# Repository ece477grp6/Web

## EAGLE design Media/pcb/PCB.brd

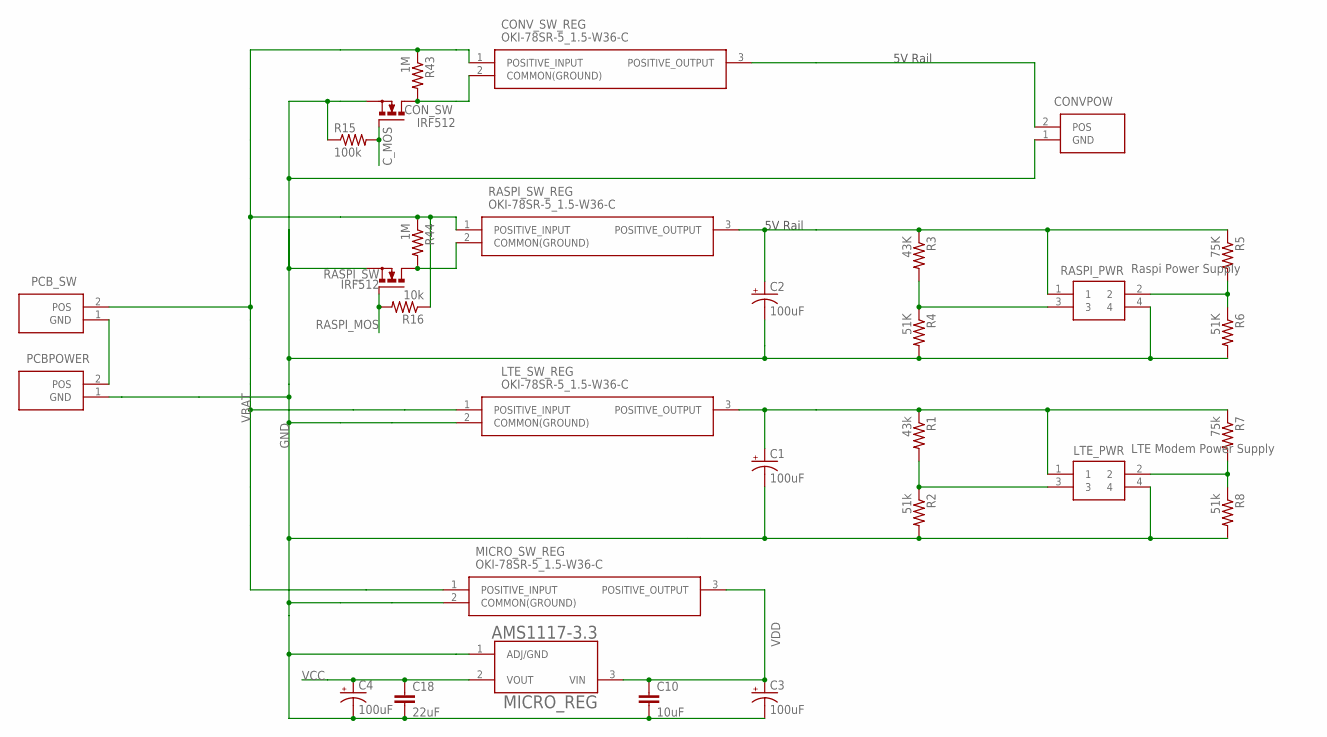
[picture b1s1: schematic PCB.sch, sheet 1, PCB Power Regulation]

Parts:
C1, C2, C3, C4: 100uF; 140CLH-0810
C10: 10uF; C0805
C18: 22uF; C0805
CONVPOW: PRT-10474; SHDR2W320P716_1X2_1574X813X158
CONV_SW_REG: OKI-78SR-5_1.5-W36-C; OKI-78SR
CON_SW: IRF512; TO220BV
LTE_PWR: LTE Modem Power Supply; 105057-0001
LTE_SW_REG: OKI-78SR-5_1.5-W36-C; OKI-78SR
MICRO_REG: AMS1117-3.3; SOT229P700X180-4N
MICRO_SW_REG: OKI-78SR-5_1.5-W36-C; OKI-78SR
PCBPOWER: PRT-10474; SHDR2W320P716_1X2_1574X813X158
PCB_SW: PRT-10474; SHDR2W320P716_1X2_1574X813X158
R1: 43k; R0805
R2, R8: 51k; R0805
R3: 43K; R0805
R4, R6: 51K; R0805
R5: 75K; R0805
R7: 75k; R0805
R15: 100k; R0805
R16: 10k; R0805
R43, R44: 1M; R0805
RASPI_PWR: Raspi Power Supply; 105057-0001
RASPI_SW: IRF512; TO220BV
RASPI_SW_REG: OKI-78SR-5_1.5-W36-C; OKI-78SR

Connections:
C_MOS: CON_SW.G, R15.2; also elsewhere on the board
GND: C1.-, C2.-, C3.-, C4.-, C10.2, C18.2, CONVPOW.1 (GND), CON_SW.S, LTE_PWR.4, LTE_SW_REG.2 (COMMON(GROUND)), MICRO_REG.1 (ADJ/GND), MICRO_SW_REG.2 (COMMON(GROUND)), PCBPOWER.1 (GND), R2.2, R4.2, R6.2, R8.2, R15.1, RASPI_PWR.4, RASPI_SW.S; also elsewhere on the board
unnamed: CONVPOW.2 (POS), CONV_SW_REG.3 (POSITIVE_OUTPUT)
unnamed: C1.+, LTE_PWR.1, LTE_SW_REG.3 (POSITIVE_OUTPUT), R1.1, R7.1
unnamed: LTE_PWR.3, R1.2, R2.1
unnamed: LTE_PWR.2, R7.2, R8.1
unnamed: CONV_SW_REG.2 (COMMON(GROUND)), CON_SW.D, R43.2
unnamed: R5.2, R6.1, RASPI_PWR.2
unnamed: R3.2, R4.1, RASPI_PWR.3
unnamed: C2.+, R3.1, R5.1, RASPI_PWR.1, RASPI_SW_REG.3 (POSITIVE_OUTPUT)
unnamed: R44.2, RASPI_SW.D, RASPI_SW_REG.2 (COMMON(GROUND))
unnamed: PCBPOWER.2 (POS), PCB_SW.1 (GND)
RASPI_MOS: R16.2, RASPI_SW.G; also elsewhere on the board
VBAT: CONV_SW_REG.1 (POSITIVE_INPUT), LTE_SW_REG.1 (POSITIVE_INPUT), MICRO_SW_REG.1 (POSITIVE_INPUT), PCB_SW.2 (POS), R16.1, R43.1, R44.1, RASPI_SW_REG.1 (POSITIVE_INPUT)
VCC: C4.+, C18.1, MICRO_REG.2 (VOUT); also elsewhere on the board
VDD: C3.+, C10.1, MICRO_REG.3 (VIN), MICRO_SW_REG.3 (POSITIVE_OUTPUT); also elsewhere on the board

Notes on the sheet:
5V Rail

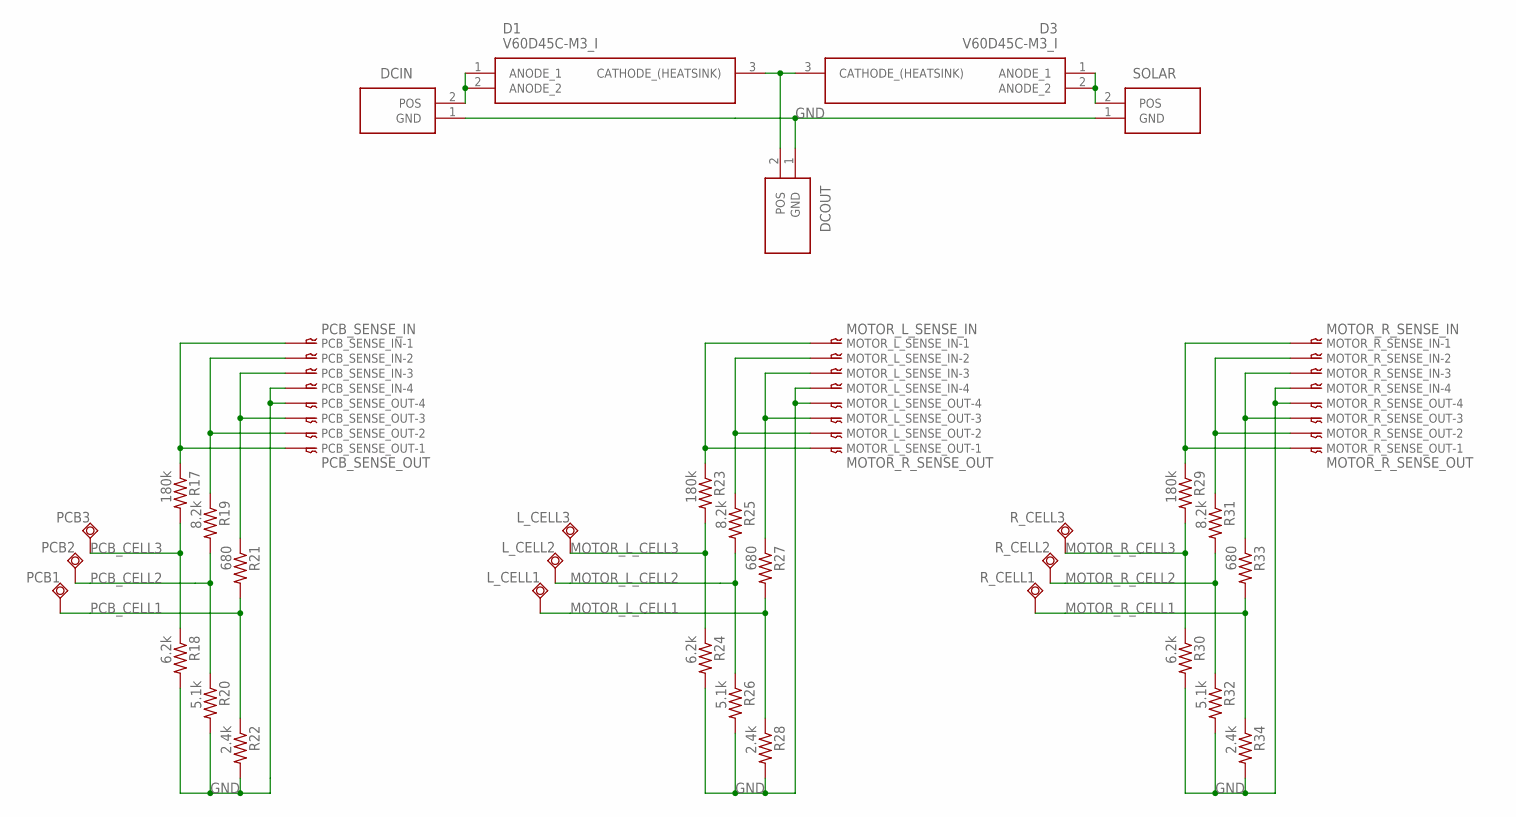
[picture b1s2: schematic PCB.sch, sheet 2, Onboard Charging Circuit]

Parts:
D1, D3: V60D45C-M3_I; TO-263AC(SMPD)
DCIN: PRT-10474; SHDR2W320P716_1X2_1574X813X158
DCOUT: PRT-10474; SHDR2W320P716_1X2_1574X813X158
L_CELL1, L_CELL2: TPSQB2,54; B2,54
L_CELL3: PCB_CELL3; B2,54
MOTOR_L_SENSE_IN: MOTOR_L_SENSE_IN; B4B-XH
MOTOR_L_SENSE_OUT: MOTOR_R_SENSE_OUT; B4B-XH
MOTOR_R_SENSE_IN: MOTOR_R_SENSE_IN; B4B-XH
MOTOR_R_SENSE_OUT: MOTOR_R_SENSE_OUT; B4B-XH
PCB1, PCB2: TPSQB2,54; B2,54
PCB3: PCB_CELL3; B2,54
PCB_SENSE_IN: PCB_SENSE_IN; B4B-XH
PCB_SENSE_OUT: PCB_SENSE_OUT; B4B-XH
R17, R23, R29: 180k; R0805
R18, R24, R30: 6.2k; R0805
R19, R25, R31: 8.2k; R0805
R20, R26, R32: 5.1k; R0805
R21, R27, R33: 680; R0805
R22, R28, R34: 2.4k; R0805
R_CELL1, R_CELL2: TPSQB2,54; B2,54
R_CELL3: PCB_CELL3; B2,54
SOLAR: PRT-10474; SHDR2W320P716_1X2_1574X813X158

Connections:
GND: DCIN.1 (GND), DCOUT.1 (GND), MOTOR_L_SENSE_IN.P$4, MOTOR_L_SENSE_OUT.P$4, MOTOR_R_SENSE_IN.P$4, MOTOR_R_SENSE_OUT.P$4, PCB_SENSE_IN.P$4, PCB_SENSE_OUT.P$4, R18.2, R20.2, R22.2, R24.2, R26.2, R28.2, R30.2, R32.2, R34.2, SOLAR.1 (GND); also elsewhere on the board
MOTOR_L_CELL1: L_CELL1.TP, R27.2, R28.1; also elsewhere on the board
MOTOR_L_CELL2: L_CELL2.TP, R25.2, R26.1; also elsewhere on the board
MOTOR_L_CELL3: L_CELL3.TP, R23.2, R24.1; also elsewhere on the board
MOTOR_R_CELL1: R33.2, R34.1, R_CELL1.TP; also elsewhere on the board
MOTOR_R_CELL2: R31.2, R32.1, R_CELL2.TP; also elsewhere on the board
MOTOR_R_CELL3: R29.2, R30.1, R_CELL3.TP; also elsewhere on the board
unnamed: PCB_SENSE_IN.P$3, PCB_SENSE_OUT.P$3, R21.1
unnamed: D1.1 (ANODE_1), D1.2 (ANODE_2), DCIN.2 (POS)
unnamed: D3.1 (ANODE_1), D3.2 (ANODE_2), SOLAR.2 (POS)
unnamed: PCB_SENSE_IN.P$1, PCB_SENSE_OUT.P$1, R17.1
unnamed: MOTOR_L_SENSE_IN.P$3, MOTOR_L_SENSE_OUT.P$3, R27.1
unnamed: MOTOR_L_SENSE_IN.P$2, MOTOR_L_SENSE_OUT.P$2, R25.1
unnamed: MOTOR_L_SENSE_IN.P$1, MOTOR_L_SENSE_OUT.P$1, R23.1
unnamed: MOTOR_R_SENSE_IN.P$3, MOTOR_R_SENSE_OUT.P$3, R33.1
unnamed: MOTOR_R_SENSE_IN.P$2, MOTOR_R_SENSE_OUT.P$2, R31.1
unnamed: PCB_SENSE_IN.P$2, PCB_SENSE_OUT.P$2, R19.1
unnamed: MOTOR_R_SENSE_IN.P$1, MOTOR_R_SENSE_OUT.P$1, R29.1
unnamed: D1.3 (CATHODE_(HEATSINK)), D3.3 (CATHODE_(HEATSINK)), DCOUT.2 (POS)
PCB_CELL1: PCB1.TP, R21.2, R22.1; also elsewhere on the board
PCB_CELL2: PCB2.TP, R19.2, R20.1; also elsewhere on the board
PCB_CELL3: PCB3.TP, R17.2, R18.1; also elsewhere on the board

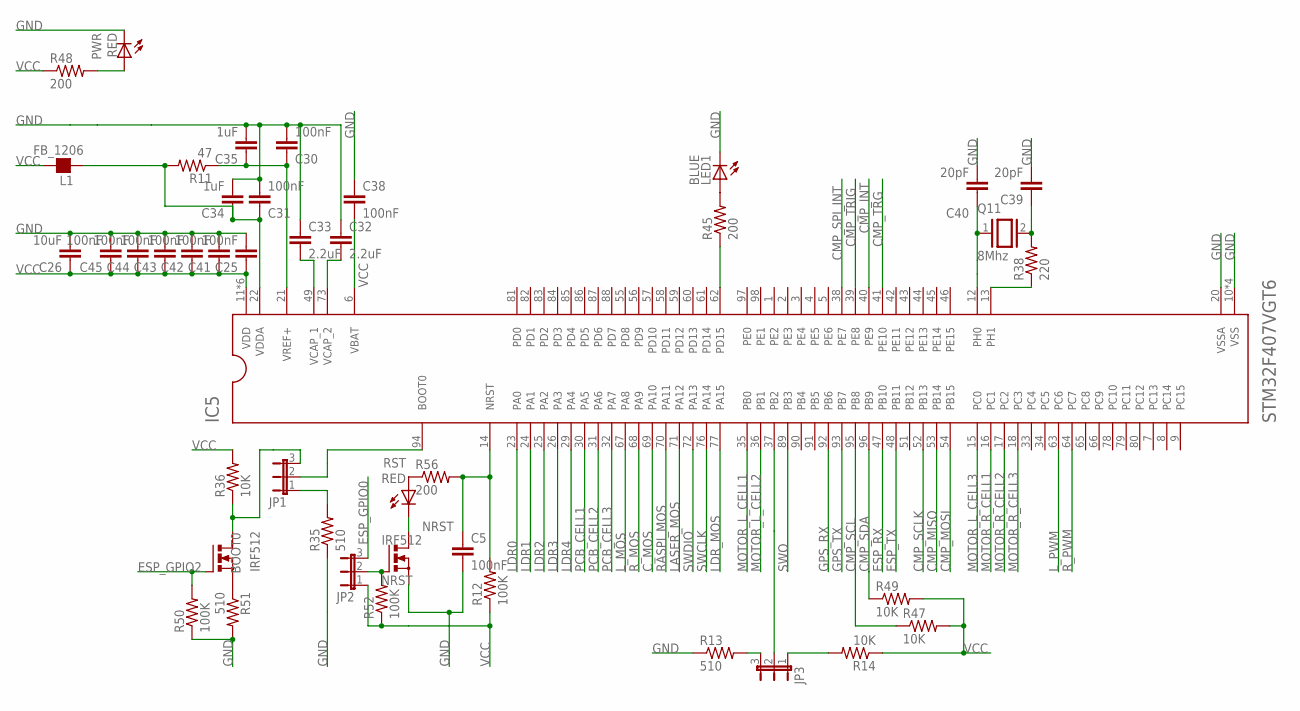
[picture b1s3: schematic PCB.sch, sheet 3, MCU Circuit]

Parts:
BOOT0: IRF512; TO220BV
C5, C25, C30, C31, C38, C41, C42, C43, C44, C45: 100nF; C0805
C26: 10uF; C0805
C32, C33: 2.2uF; C0805
C34, C35: 1uF; C0805
C39, C40: 20pF; C0805
IC5: STM32F407VGT6; QFP50P1600X1600X160-100N
JP1, JP2, JP3: JP2E; JP2
L1: FB_1206; L1206
LED1: BLUE; CHIPLED_0805
NRST: IRF512; TO220BV
PWR: RED; CHIPLED_0805
Q11: 8Mhz; QS
R11: 47; R0805
R12, R50, R52: 100K; R0805
R13, R35, R51: 510; R0805
R14, R36, R47, R49: 10K; R0805
R38: 220; R0805
R45, R48, R56: 200; R0805
RST: RED; CHIPLED_0805

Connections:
CMP_INT: IC5.40 (PE9); also elsewhere on the board
CMP_MISO: IC5.53 (PB14); also elsewhere on the board
CMP_MOSI: IC5.54 (PB15); also elsewhere on the board
CMP_SCL: IC5.95 (PB8), R47.1; also elsewhere on the board
CMP_SCLK: IC5.52 (PB13); also elsewhere on the board
CMP_SDA: IC5.96 (PB9), R49.1; also elsewhere on the board
CMP_SPI_INT: IC5.38 (PE7); also elsewhere on the board
CMP_TRG: IC5.41 (PE10); also elsewhere on the board
CMP_TRIG: IC5.39 (PE8); also elsewhere on the board
C_MOS: IC5.69 (PA10); also elsewhere on the board
ESP_GPIO0: JP2.3; also elsewhere on the board
ESP_GPIO2: BOOT0.G, R50.2; also elsewhere on the board
ESP_RX: IC5.47 (PB10); also elsewhere on the board
ESP_TX: IC5.48 (PB11); also elsewhere on the board
GND: C5.2, C25.2, C26.2, C30.2, C31.2, C32.1, C33.1, C34.2, C35.2, C38.1, C39.2, C40.2, C41.2, C42.2, C43.2, C44.2, C45.2, IC5.10 (VSS), IC5.20 (VSSA), IC5.27 (VSS), IC5.74 (VSS), IC5.99 (VSS), LED1.C, NRST.S, PWR.C, R13.1, R35.1, R50.1, R51.2; also elsewhere on the board
GPS_RX: IC5.92 (PB6); also elsewhere on the board
GPS_TX: IC5.93 (PB7); also elsewhere on the board
LASER_MOS: IC5.71 (PA12); also elsewhere on the board
LDR0: IC5.23 (PA0); also elsewhere on the board
LDR1: IC5.24 (PA1); also elsewhere on the board
LDR2: IC5.25 (PA2); also elsewhere on the board
LDR3: IC5.26 (PA3); also elsewhere on the board
LDR4: IC5.29 (PA4); also elsewhere on the board
LDR_MOS: IC5.77 (PA15); also elsewhere on the board
L_MOS: IC5.67 (PA8); also elsewhere on the board
L_PWM: IC5.63 (PC6); also elsewhere on the board
MOTOR_L_CELL1: IC5.35 (PB0); also elsewhere on the board
MOTOR_L_CELL2: IC5.36 (PB1); also elsewhere on the board
MOTOR_L_CELL3: IC5.15 (PC0); also elsewhere on the board
MOTOR_R_CELL1: IC5.16 (PC1); also elsewhere on the board
MOTOR_R_CELL2: IC5.17 (PC2); also elsewhere on the board
MOTOR_R_CELL3: IC5.18 (PC3); also elsewhere on the board
unnamed: IC5.37 (PB2), JP3.2
unnamed: C32.2, IC5.73 (VCAP_2)
unnamed: R56.1, RST.A
unnamed: C33.2, IC5.49 (VCAP_1)
unnamed: PWR.A, R48.2
unnamed: JP3.1, R14.2
unnamed: C30.1, C35.1, IC5.21 (VREF+), R11.1
unnamed: C31.1, C34.1, IC5.22 (VDDA), L1.1, R11.2
unnamed: IC5.62 (PD15), R45.1
unnamed: JP2.2, NRST.G, R52.2
unnamed: BOOT0.S, R51.1
unnamed: LED1.A, R45.2
unnamed: C5.1, IC5.14 (NRST), R12.2, R56.2
unnamed: IC5.13 (PH1), R38.1
unnamed: IC5.94 (BOOT0), JP1.2
unnamed: JP1.1, R35.2
unnamed: C39.1, Q11.2, R38.2
unnamed: BOOT0.D, JP1.3, R36.1
unnamed: C40.1, IC5.12 (PH0), Q11.1
unnamed: JP3.3, R13.2
NRST: NRST.D, RST.C; also elsewhere on the board
PCB_CELL1: IC5.30 (PA5); also elsewhere on the board
PCB_CELL2: IC5.31 (PA6); also elsewhere on the board
PCB_CELL3: IC5.32 (PA7); also elsewhere on the board
RASPI_MOS: IC5.70 (PA11); also elsewhere on the board
R_MOS: IC5.68 (PA9); also elsewhere on the board
R_PWM: IC5.64 (PC7); also elsewhere on the board
SWCLK: IC5.76 (PA14); also elsewhere on the board
SWDIO: IC5.72 (PA13); also elsewhere on the board
SWO: IC5.89 (PB3); also elsewhere on the board
VCC: C25.1, C26.1, C38.2, C41.1, C42.1, C43.1, C44.1, C45.1, IC5.6 (VBAT), IC5.11 (VDD), IC5.19 (VDD), IC5.28 (VDD), IC5.50 (VDD), IC5.75 (VDD), IC5.100 (VDD), JP2.1, L1.2, R12.1, R14.1, R36.2, R47.2, R48.1, R49.2, R52.1; also elsewhere on the board

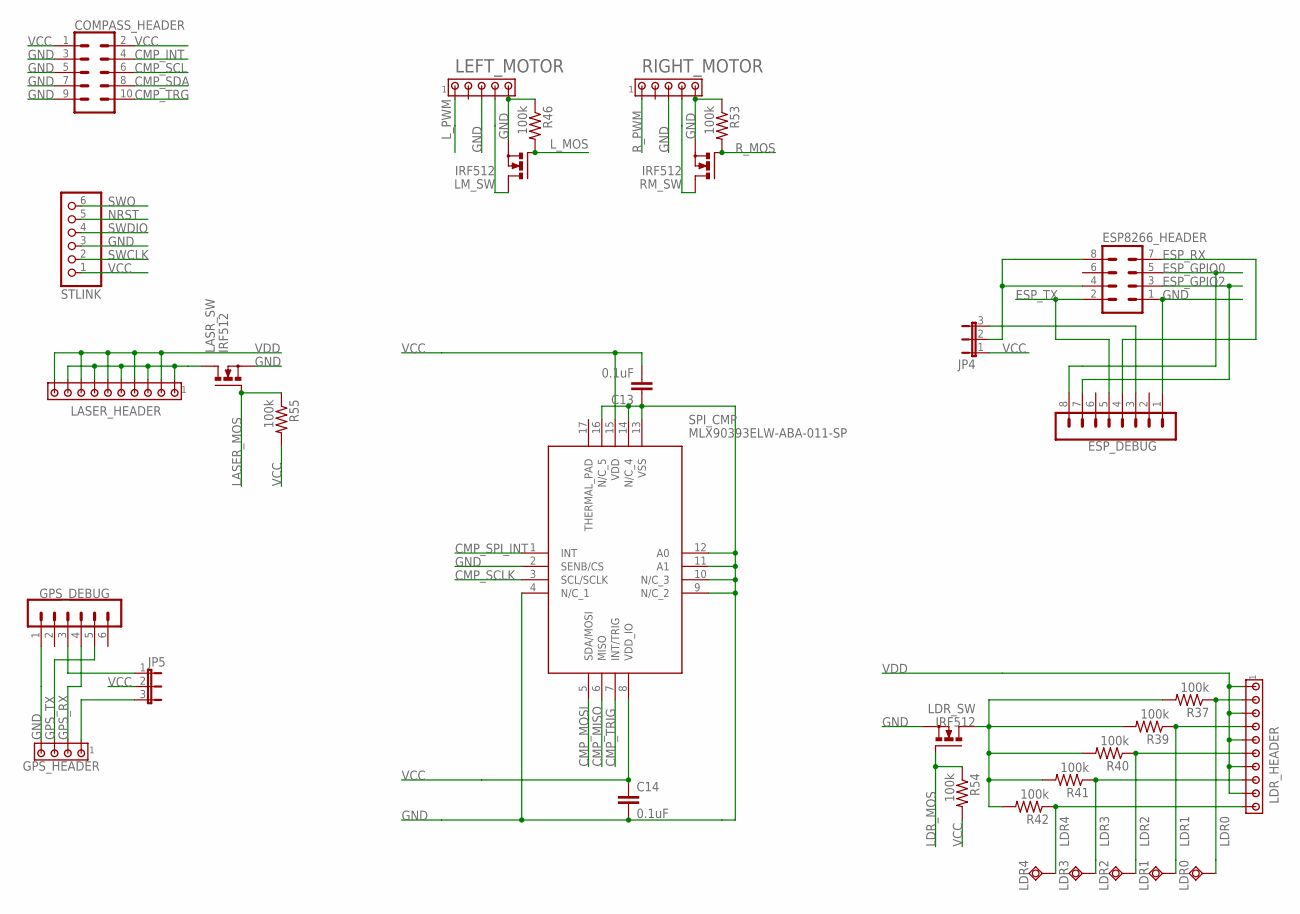
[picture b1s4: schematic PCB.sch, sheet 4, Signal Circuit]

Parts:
C13, C14: 0.1uF; C1206
COMPASS_HEADER: CONN_05X2SHD; 2X5-SHROUDED
ESP8266_HEADER: MA04-2
ESP_DEBUG: MA08-1
GPS_DEBUG: MA06-1
GPS_HEADER: MTA04-100; 10X04MTA
JP4, JP5: JP2E; JP2
LASER_HEADER: MTA10-100; 10X10MTA
LASR_SW: IRF512; TO220BV
LDR0, LDR1, LDR2, LDR3, LDR4: TPSQB2,54; B2,54
LDR_HEADER: MTA10-100; 10X10MTA
LDR_SW: IRF512; TO220BV
LEFT_MOTOR: MTA05-100; 1X05MTA
LM_SW: IRF512; TO220BV
R37, R39, R40, R41, R42, R46, R53, R54, R55: 100k; R1206
RIGHT_MOTOR: MTA05-100; 1X05MTA
RM_SW: IRF512; TO220BV
SPI_CMP: MLX90393ELW-ABA-011-SP; QFN50P300X300X100-17N
STLINK: PINHD-1X6; 1X06

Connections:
CMP_INT: COMPASS_HEADER.4; also elsewhere on the board
CMP_MISO: SPI_CMP.6 (MISO); also elsewhere on the board
CMP_MOSI: SPI_CMP.5 (SDA/MOSI); also elsewhere on the board
CMP_SCL: COMPASS_HEADER.6; also elsewhere on the board
CMP_SCLK: SPI_CMP.3 (SCL/SCLK); also elsewhere on the board
CMP_SDA: COMPASS_HEADER.8; also elsewhere on the board
CMP_SPI_INT: SPI_CMP.1 (INT); also elsewhere on the board
CMP_TRG: COMPASS_HEADER.10; also elsewhere on the board
CMP_TRIG: SPI_CMP.7 (INT/TRIG); also elsewhere on the board
ESP_GPIO0: ESP8266_HEADER.5, ESP_DEBUG.8; also elsewhere on the board
ESP_GPIO2: ESP8266_HEADER.3, ESP_DEBUG.7; also elsewhere on the board
ESP_RX: ESP8266_HEADER.7, ESP_DEBUG.4; also elsewhere on the board
ESP_TX: ESP8266_HEADER.2, ESP_DEBUG.5; also elsewhere on the board
GND: C13.1, C14.2, COMPASS_HEADER.3, COMPASS_HEADER.5, COMPASS_HEADER.7, COMPASS_HEADER.9, ESP8266_HEADER.1, ESP_DEBUG.1, GPS_DEBUG.1, GPS_HEADER.4, LASR_SW.S, LDR_SW.S, LEFT_MOTOR.3, LEFT_MOTOR.5, LM_SW.S, R46.1, R53.1, RIGHT_MOTOR.3, RIGHT_MOTOR.5, RM_SW.S, SPI_CMP.2 (SENB/CS), SPI_CMP.4 (N/C_1), SPI_CMP.9 (N/C_2), SPI_CMP.10 (N/C_3), SPI_CMP.11 (A1), SPI_CMP.12 (A0), SPI_CMP.13 (VSS), SPI_CMP.14 (N/C_4), SPI_CMP.16 (N/C_5), STLINK.3; also elsewhere on the board
GPS_RX: GPS_DEBUG.4, GPS_HEADER.2; also elsewhere on the board
GPS_TX: GPS_DEBUG.5, GPS_HEADER.3; also elsewhere on the board
LASER_MOS: LASR_SW.G, R55.1; also elsewhere on the board
LDR0: LDR0.TP, LDR_HEADER.2, R37.1; also elsewhere on the board
LDR1: LDR1.TP, LDR_HEADER.4, R39.1; also elsewhere on the board
LDR2: LDR2.TP, LDR_HEADER.6, R40.1; also elsewhere on the board
LDR3: LDR3.TP, LDR_HEADER.8, R41.1; also elsewhere on the board
LDR4: LDR4.TP, LDR_HEADER.10, R42.1; also elsewhere on the board
LDR_MOS: LDR_SW.G, R54.1; also elsewhere on the board
L_MOS: LM_SW.G, R46.2; also elsewhere on the board
L_PWM: LEFT_MOTOR.1; also elsewhere on the board
unnamed: LEFT_MOTOR.4, LM_SW.D
unnamed: ESP_DEBUG.3, JP4.3
unnamed: GPS_DEBUG.3, JP5.1
unnamed: LDR_SW.D, R37.2, R39.2, R40.2, R41.2, R42.2
unnamed: ESP8266_HEADER.4, ESP8266_HEADER.8, JP4.2
unnamed: GPS_HEADER.1, JP5.3
unnamed: LASER_HEADER.1, LASER_HEADER.3, LASER_HEADER.5, LASER_HEADER.7, LASER_HEADER.9, LASR_SW.D
unnamed: RIGHT_MOTOR.4, RM_SW.D
NRST: STLINK.5; also elsewhere on the board
R_MOS: R53.2, RM_SW.G; also elsewhere on the board
R_PWM: RIGHT_MOTOR.1; also elsewhere on the board
SWCLK: STLINK.2; also elsewhere on the board
SWDIO: STLINK.4; also elsewhere on the board
SWO: STLINK.6; also elsewhere on the board
VCC: C13.2, C14.1, COMPASS_HEADER.1, COMPASS_HEADER.2, JP4.1, JP5.2, R54.2, R55.2, SPI_CMP.8 (VDD_IO), SPI_CMP.15 (VDD), STLINK.1; also elsewhere on the board
VDD: LASER_HEADER.2, LASER_HEADER.4, LASER_HEADER.6, LASER_HEADER.8, LASER_HEADER.10, LDR_HEADER.1, LDR_HEADER.3, LDR_HEADER.5, LDR_HEADER.7, LDR_HEADER.9; also elsewhere on the board

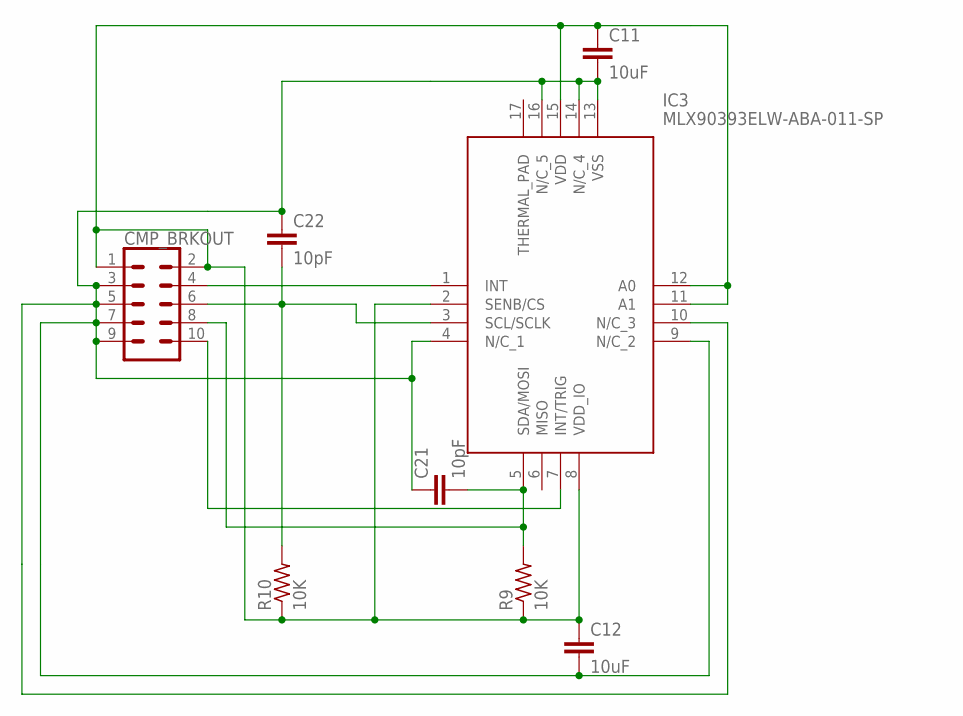
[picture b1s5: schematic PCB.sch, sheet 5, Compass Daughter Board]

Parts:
C11, C12: 10uF; C1206
C21, C22: 10pF; C1206
CMP_BRKOUT: CONN_05X2SHD; 2X5-SHROUDED
IC3: MLX90393ELW-ABA-011-SP; QFN50P300X300X100-17N
R9, R10: 10K; R1206

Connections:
unnamed: C11.2, C12.2, C21.1, C22.1, CMP_BRKOUT.3, CMP_BRKOUT.5, CMP_BRKOUT.7, CMP_BRKOUT.9, IC3.4 (N/C_1), IC3.9 (N/C_2), IC3.10 (N/C_3), IC3.13 (VSS), IC3.14 (N/C_4), IC3.16 (N/C_5)
unnamed: CMP_BRKOUT.4, IC3.1 (INT)
unnamed: C22.2, CMP_BRKOUT.6, IC3.3 (SCL/SCLK), R10.2
unnamed: C21.2, CMP_BRKOUT.8, IC3.5 (SDA/MOSI), R9.2
unnamed: CMP_BRKOUT.10, IC3.7 (INT/TRIG)
unnamed: C11.1, C12.1, CMP_BRKOUT.1, CMP_BRKOUT.2, IC3.2 (SENB/CS), IC3.8 (VDD_IO), IC3.11 (A1), IC3.12 (A0), IC3.15 (VDD), R9.1, R10.1

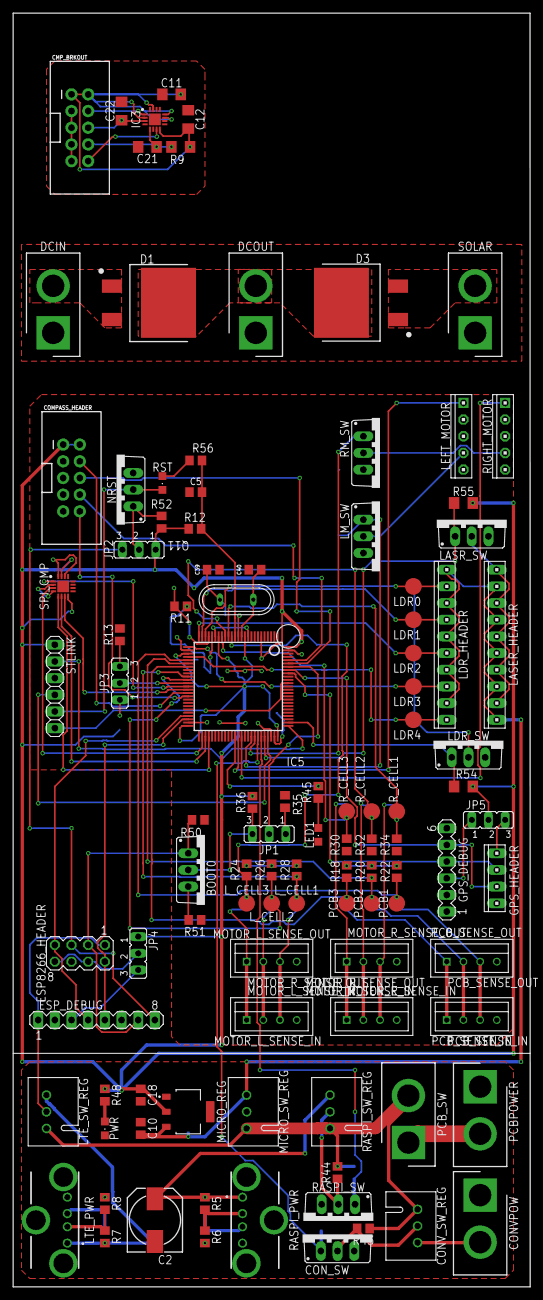
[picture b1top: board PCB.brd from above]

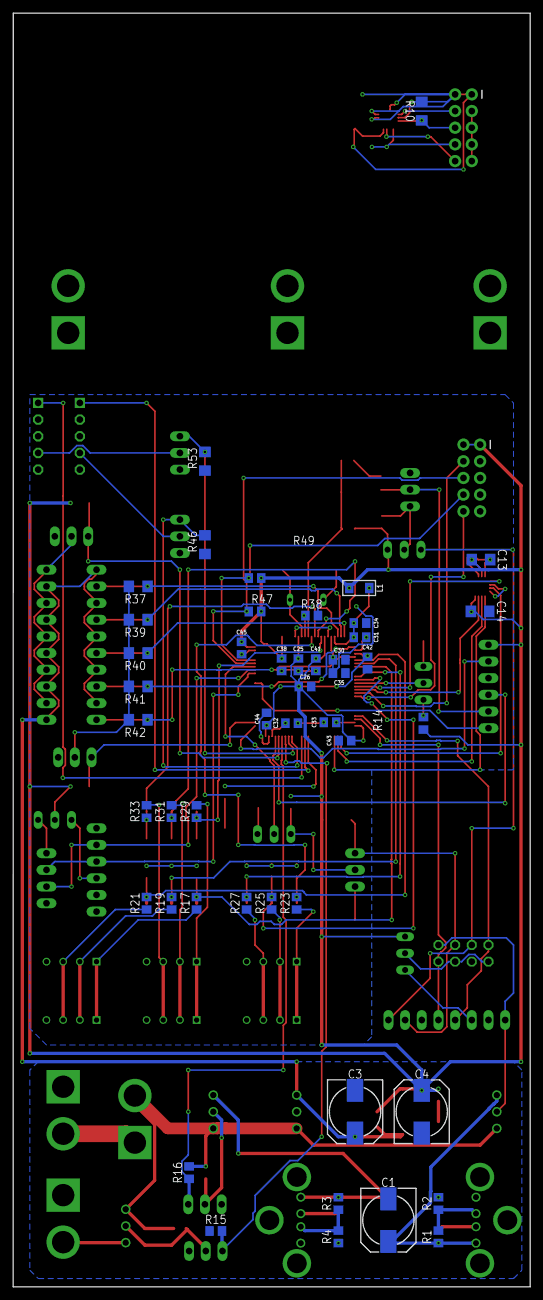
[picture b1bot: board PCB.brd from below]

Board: 2 copper layers, 78.7 x 194.0 mm, 152 parts (47 on the bottom side), 101 nets.

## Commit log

2018-08-22 initialize web
2018-08-24 update base address to preview/477grp6 in index
2018-08-24 updated contact info, changed index back to initial page
2018-08-24 updated navbar to include Tianjie JIa email address
2018-08-27 updated some team info
2018-08-28 add rebase script
2018-08-28 fixed rebase script
2018-08-28 remove team org
2018-08-28 fixed redirection
2018-08-28 fix final url
2018-08-28 redirect final url
2018-08-29 fixed website link issue
2018-08-29 fixed reference link to github
2018-08-29 update team info with hyperlink
2018-08-29 addded team info
2018-08-29 fix typo
2018-08-29 renamed progress files and updated progress links to files
2018-08-29 fixed formatting
2018-08-29 update personal info
2018-08-29 Adding Shuang's image
2018-08-29 moving shuang's image
2018-08-29 photo
2018-08-29 update picture
2018-08-30 change
2018-08-30 insert name for shuangliu
2018-08-31 fixed personal description, start team progress report
2018-08-31 removed ._*
2018-08-31 fixed gitignore
2018-08-31 update Week 1 progress report
2018-08-31 update progress report for week 2
2018-08-31 update FinalProjectProposal hyperlink and InitialProjectProposal hyperlink
2018-08-31 add supporting files
2018-08-31 update file structure
2018-08-31 renamed folder
2018-08-31 autoupdate script
2018-08-31 fixed script
2018-08-31 ignore autoupdate.sh
2018-08-31 fix script
2018-08-31 test
2018-08-31 fix gitignore
2018-08-31 added nohup
2018-08-31 removed files
2018-08-31 upload tianjie photo
2018-08-31 adding shuang's progress
2018-08-31 adding shuang
2018-08-31 change photo
2018-08-31 update documents
2018-08-31 fixed non-deleteion of template
2018-08-31 update progress report
2018-08-31 update PSSC
2018-08-31 week2
2018-08-31 description
2018-09-03 Update to file structure
2018-09-04 update to personal progress report
2018-09-04 updated code style
2018-09-04 update css
2018-09-04 changed spacing for code
2018-09-04 change precode wrap
2018-09-04 update code style
2018-09-04 change to no wrap
2018-09-04 testing
2018-09-04 change skin
2018-09-04 pretty codes by google
2018-09-04 add pic of log
2018-09-04 fixed typos
2018-09-04 rebase
2018-09-04 fix width
2018-09-04 LDR circuit
2018-09-04 accept incoming change
2018-09-04 change to html5
2018-09-05 update team progress
2018-09-05 Week3
2018-09-06 change liu's adder
2018-09-06 updating progress report
2018-09-06 updating
2018-09-06 shuang update
2018-09-06 fix link
2018-09-07 Upload files
2018-09-07 added reference
2018-09-07 week 3 progress report
2018-09-13 pics
2018-09-13 circuit
2018-09-14 fixed formatting issue
2018-09-15 Shitty Alignment
2018-09-15 trying so hard
2018-09-15 fix div
2018-09-15 revert changes
2018-09-15 fix?
2018-09-15 footer fix
2018-09-15 add one pic
2018-09-15 fix height
2018-09-15 fixx
2018-09-15 forced fix
2018-09-15 add space consistency
2018-09-15 add space
2018-09-21 update report
2018-09-21 update with code
2018-09-21 updated code
2018-09-29 add screenshot of yuv streaming
2018-09-29 progress update
2018-10-05 pictures
2018-10-05 week 7
2018-10-06 work in progress
2018-10-06 update weekly progress
2018-10-06 fix width issue
2018-10-06 fix margin
2018-10-06 fix hyperlink
2018-10-06 fix format
2018-10-10 added PCB layout
2018-10-10 fixed layout and schematics
2018-10-10 major update
2018-10-10 upodate
2018-10-10 fixed presentation
2018-10-10 fix path to ppt
2018-10-27 fix formatting
2018-10-27 week10
2018-11-03 week 11
2018-11-10 week 12
2018-11-10 fix layout
2018-11-17 week 13
2018-12-01 week15
2018-12-12 add final

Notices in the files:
parts and their libraries:
SparkFun-Connectors: Licensing: Creative Commons ShareAlike 4.0 International - https://creativecommons.org/licenses/by-sa/4.0
rc-master-smd: Copyright (C) 2007, Bob Starr
